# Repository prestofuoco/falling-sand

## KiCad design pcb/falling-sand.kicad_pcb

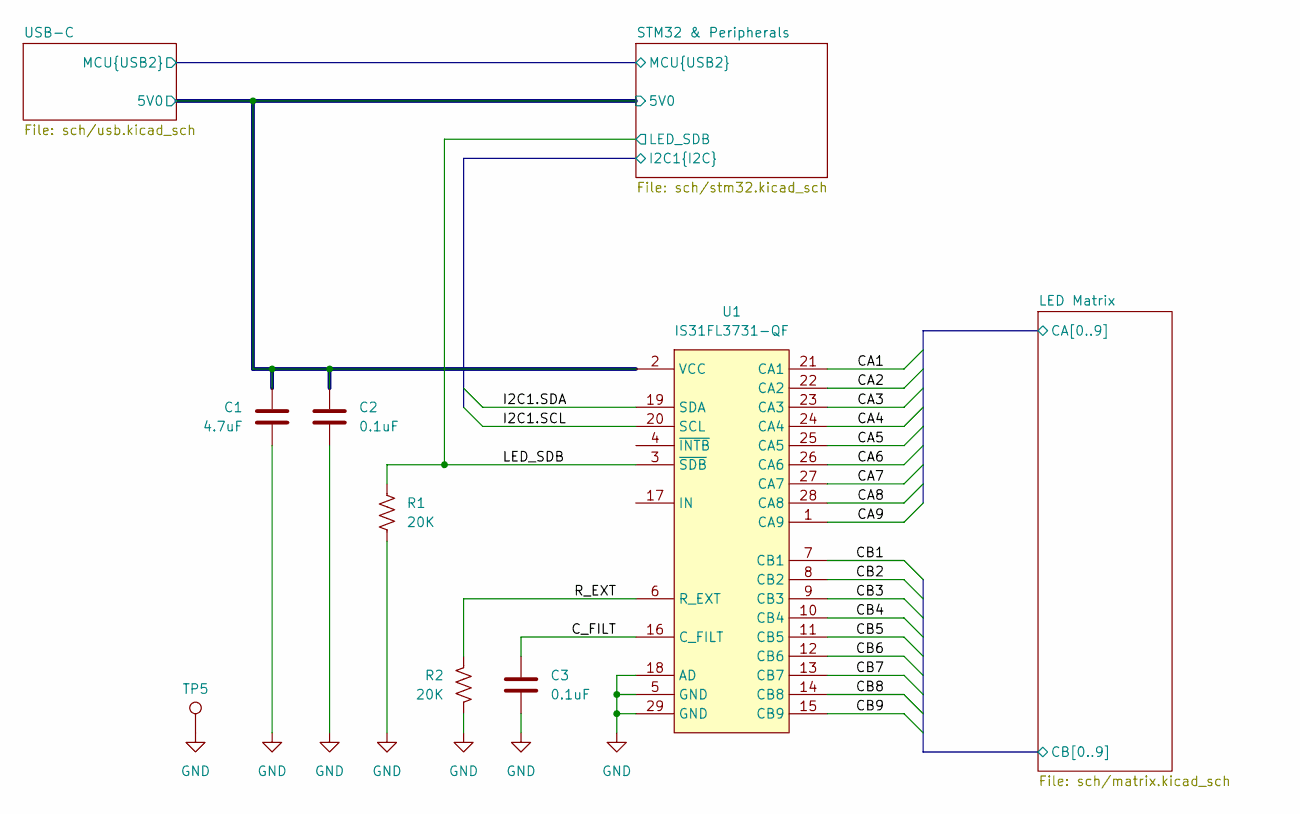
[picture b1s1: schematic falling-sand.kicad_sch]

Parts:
C1: 4.7uF; C_0603_1608Metric
C2, C3: 0.1uF; C_0402_1005Metric
R1, R2: 20K; R_0402_1005Metric
TP5: TestPoint; TestPoint_Pad_D1.0mm
U1: IS31FL3731-QF; QFN-28-1EP_4x4mm_P0.4mm_EP2.4x2.4mm

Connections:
/C_FILT: C3.1, U1.16 (C_FILT)
/LED Matrix/CA1: U1.21 (CA1); also elsewhere on the board
/LED Matrix/CA2: U1.22 (CA2); also elsewhere on the board
/LED Matrix/CA3: U1.23 (CA3); also elsewhere on the board
/LED Matrix/CA4: U1.24 (CA4); also elsewhere on the board
/LED Matrix/CA5: U1.25 (CA5); also elsewhere on the board
/LED Matrix/CA6: U1.26 (CA6); also elsewhere on the board
/LED Matrix/CA7: U1.27 (CA7); also elsewhere on the board
/LED Matrix/CA8: U1.28 (CA8); also elsewhere on the board
/LED Matrix/CA9: U1.1 (CA9); also elsewhere on the board
/LED Matrix/CB1: U1.7 (CB1); also elsewhere on the board
/LED Matrix/CB2: U1.8 (CB2); also elsewhere on the board
/LED Matrix/CB3: U1.9 (CB3); also elsewhere on the board
/LED Matrix/CB4: U1.10 (CB4); also elsewhere on the board
/LED Matrix/CB5: U1.11 (CB5); also elsewhere on the board
/LED Matrix/CB6: U1.12 (CB6); also elsewhere on the board
/LED Matrix/CB7: U1.13 (CB7); also elsewhere on the board
/LED Matrix/CB8: U1.14 (CB8); also elsewhere on the board
/LED Matrix/CB9: U1.15 (CB9); also elsewhere on the board
/LED_SDB: R1.1, U1.3 (~SDB); also elsewhere on the board
/R_EXT: R2.1, U1.6 (R_EXT)
/STM32 & Peripherals/5V0: C1.1, C2.1, U1.2 (VCC); also elsewhere on the board
/STM32 & Peripherals/I2C1.SCL: U1.20 (SCL); also elsewhere on the board
/STM32 & Peripherals/I2C1.SDA: U1.19 (SDA); also elsewhere on the board
GND: C1.2, C2.2, C3.2, R1.2, R2.2, TP5.1 (1_1), U1.5 (GND), U1.18 (AD), U1.29 (GND); also elsewhere on the board

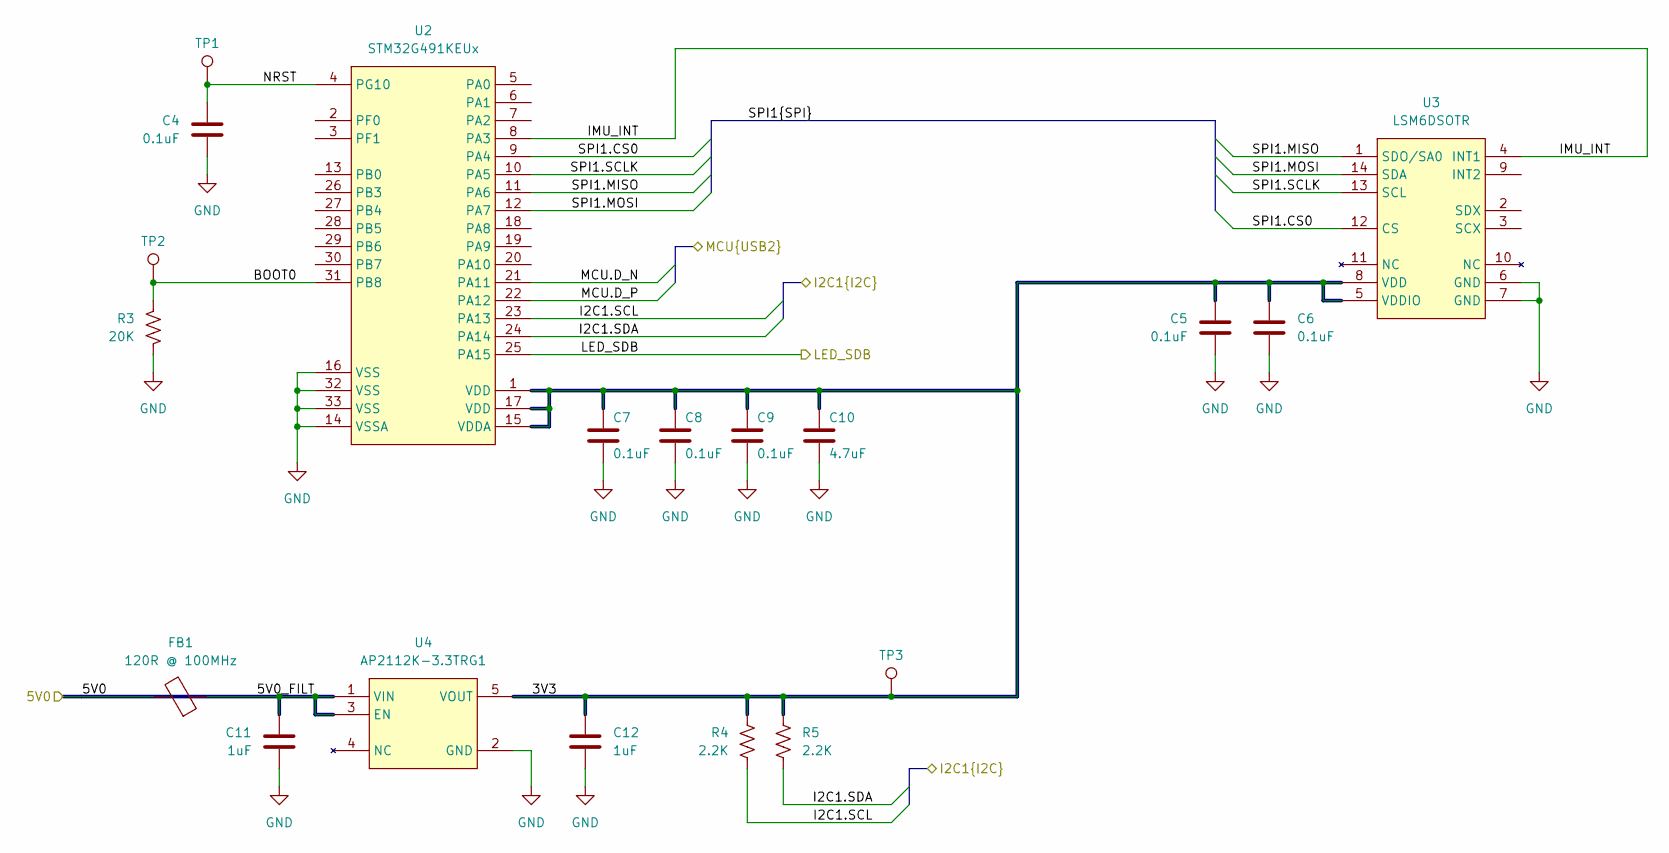
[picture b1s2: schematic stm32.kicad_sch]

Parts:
C4, C5, C6, C7, C8, C9: 0.1uF; C_0402_1005Metric
C10: 4.7uF; C_0603_1608Metric
C11, C12: 1uF; C_0603_1608Metric
FB1: 120R @ 100MHz; L_0805_2012Metric
R3: 20K; R_0402_1005Metric
R4, R5: 2.2K; R_0402_1005Metric
TP1, TP2, TP3: TestPoint; TestPoint_Pad_D1.0mm
U2: STM32G491KEUx; QFN-32-1EP_5x5mm_P0.5mm_EP3.45x3.45mm
U3: LSM6DSOTR; LGA-14_3x2.5mm_P0.5mm_LayoutBorder3x4y
U4: AP2112K-3.3TRG1; SOT-23-5

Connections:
/LED_SDB: U2.25 (PA15); also elsewhere on the board
/STM32 & Peripherals/3V3: C5.1, C6.1, C7.1, C8.1, C9.1, C10.1, C12.1, R4.1, R5.1, TP3.1 (1_1), U2.1 (VDD), U2.15 (VDDA), U2.17 (VDD), U3.5 (VDDIO), U3.8 (VDD), U4.5 (VOUT)
/STM32 & Peripherals/5V0: FB1.2; also elsewhere on the board
/STM32 & Peripherals/5V0_FILT: C11.1, FB1.1, U4.1 (VIN), U4.3 (EN)
/STM32 & Peripherals/BOOT0: R3.1, TP2.1 (1_1), U2.31 (PB8)
/STM32 & Peripherals/I2C1.SCL: R4.2, U2.23 (PA13); also elsewhere on the board
/STM32 & Peripherals/I2C1.SDA: R5.2, U2.24 (PA14); also elsewhere on the board
/STM32 & Peripherals/IMU_INT: U2.8 (PA3), U3.4 (INT1)
/STM32 & Peripherals/MCU.D_N: U2.21 (PA11); also elsewhere on the board
/STM32 & Peripherals/MCU.D_P: U2.22 (PA12); also elsewhere on the board
/STM32 & Peripherals/NRST: C4.1, TP1.1 (1_1), U2.4 (PG10)
/STM32 & Peripherals/SPI1.CS0: U2.9 (PA4), U3.12 (CS)
/STM32 & Peripherals/SPI1.MISO: U2.11 (PA6), U3.1 (SDO/SA0)
/STM32 & Peripherals/SPI1.MOSI: U2.12 (PA7), U3.14 (SDA)
/STM32 & Peripherals/SPI1.SCLK: U2.10 (PA5), U3.13 (SCL)
GND: C4.2, C5.2, C6.2, C7.2, C8.2, C9.2, C10.2, C11.2, C12.2, R3.2, U2.14 (VSSA), U2.16 (VSS), U2.32 (VSS), U2.33 (VSS), U3.6 (GND), U3.7 (GND), U4.2 (GND); also elsewhere on the board

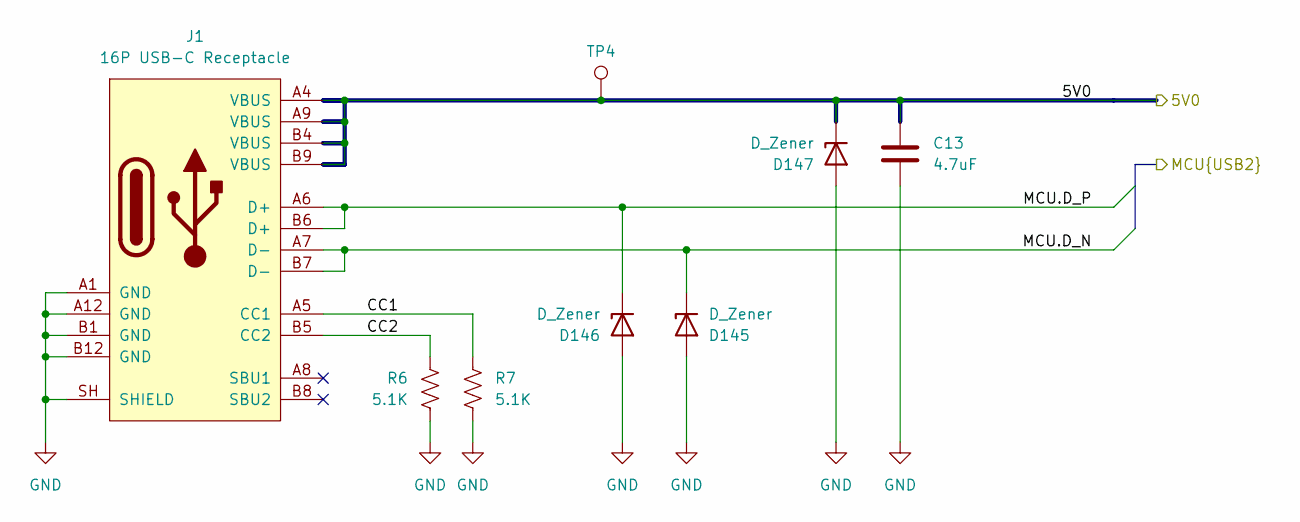
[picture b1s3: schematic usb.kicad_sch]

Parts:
C13: 4.7uF; C_0603_1608Metric
D145, D146, D147: D_Zener; D_SOD-882
J1: 16P USB-C Receptacle; USB_C_Receptacle_GCT_USB4105-xx-A_16P_TopMnt_Horizontal
R6, R7: 5.1K; R_0402_1005Metric
TP4: TestPoint; TestPoint_Pad_D1.0mm

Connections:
/STM32 & Peripherals/5V0: C13.1, D147.1 (K), J1.A4 (VBUS), J1.A9 (VBUS), J1.B4 (VBUS), J1.B9 (VBUS), TP4.1 (1_1); also elsewhere on the board
/STM32 & Peripherals/MCU.D_N: D145.1 (K), J1.A7 (D-), J1.B7 (D-); also elsewhere on the board
/STM32 & Peripherals/MCU.D_P: D146.1 (K), J1.A6 (D+), J1.B6 (D+); also elsewhere on the board
/USB-C/CC1: J1.A5 (CC1), R7.1
/USB-C/CC2: J1.B5 (CC2), R6.1
GND: C13.2, D145.2 (A), D146.2 (A), D147.2 (A), J1.A1 (GND), J1.A12 (GND), J1.B1 (GND), J1.B12 (GND), J1.SH (SHIELD), R6.2, R7.2; also elsewhere on the board

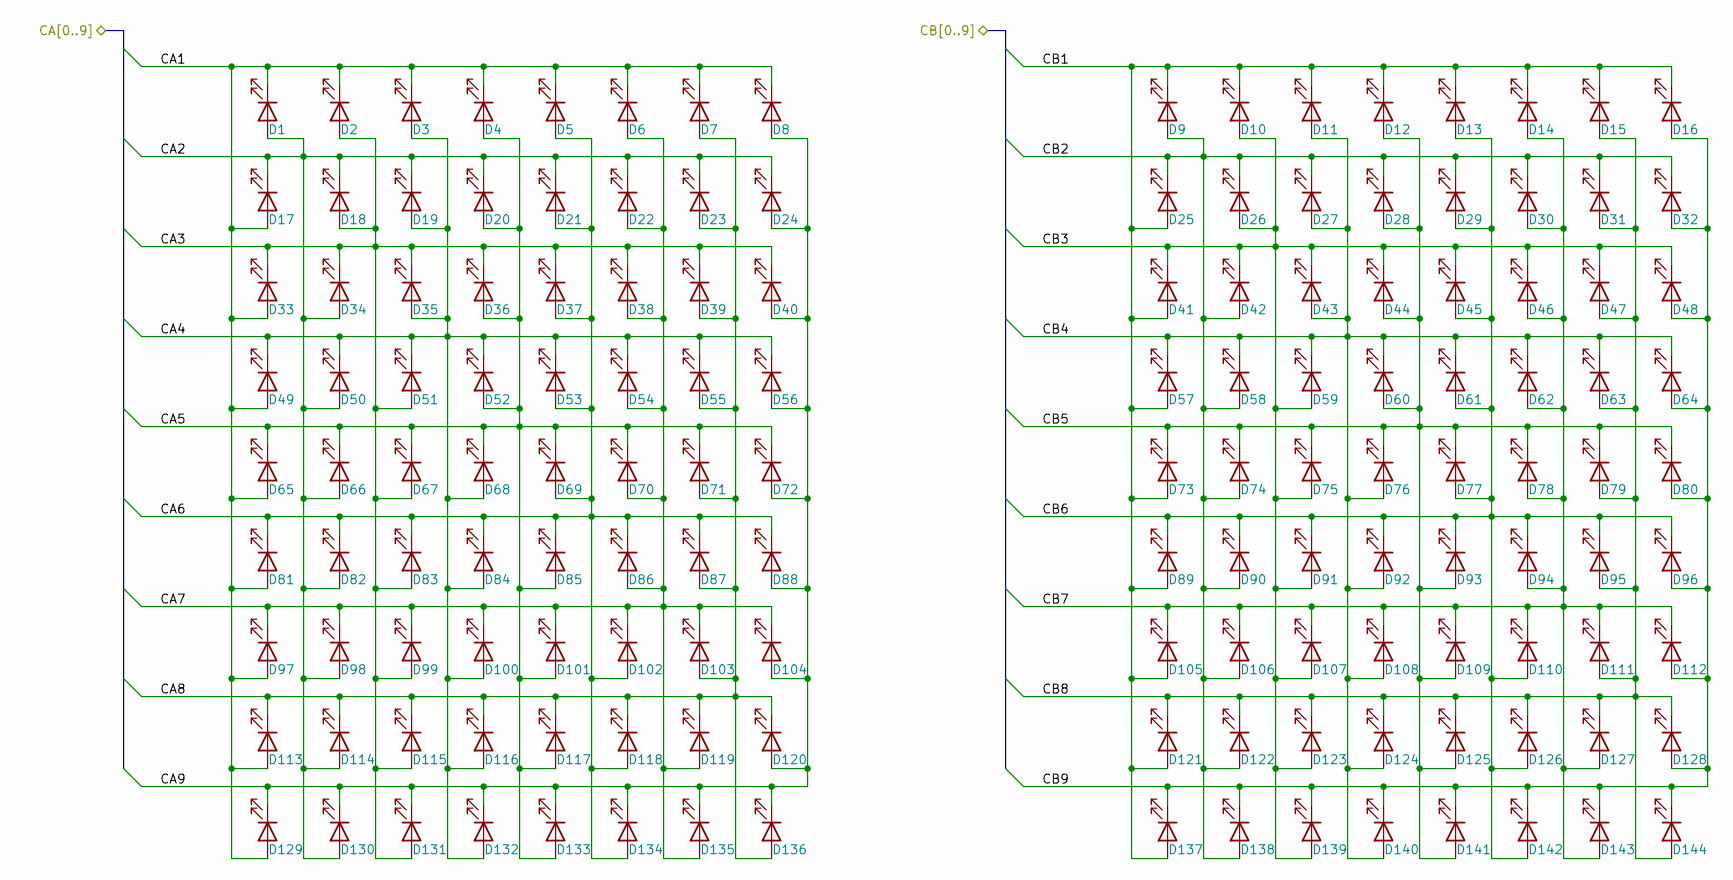
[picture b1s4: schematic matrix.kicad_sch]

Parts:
D1, D2, D3, D4, D5, D6, D7, D8, D9, D10, D11, D12, D13, D14, D15, D16, D17, D18, D19, D20, D21, D22, D23, D24, D25, D26, D27, D28, D29, D30, D31, D32, D33, D34, D35, D36, D37, D38, D39, D40, D41, D42, D43, D44, D45, D46, D47, D48, D49, D50, D51, D52, D53, D54, D55, D56, D57, D58, D59, D60, D61, D62, D63, D64, D65, D66, D67, D68, D69, D70, D71, D72, D73, D74, D75, D76, D77, D78, D79, D80, D81, D82, D83, D84, D85, D86, D87, D88, D89, D90, D91, D92, D93, D94, D95, D96, D97, D98, D99, D100, D101, D102, D103, D104, D105, D106, D107, D108, D109, D110, D111, D112, D113, D114, D115, D116, D117, D118, D119, D120, D121, D122, D123, D124, D125, D126, D127, D128, D129, D130, D131, D132, D133, D134, D135, D136, D137, D138, D139, D140, D141, D142, D143, D144: LED; LED_0402_1005Metric

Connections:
/LED Matrix/CA1: D1.1 (K), D2.1 (K), D3.1 (K), D4.1 (K), D5.1 (K), D6.1 (K), D7.1 (K), D8.1 (K), D17.2 (A), D33.2 (A), D49.2 (A), D65.2 (A), D81.2 (A), D97.2 (A), D113.2 (A), D129.2 (A); also elsewhere on the board
/LED Matrix/CA2: D1.2 (A), D17.1 (K), D18.1 (K), D19.1 (K), D20.1 (K), D21.1 (K), D22.1 (K), D23.1 (K), D24.1 (K), D34.2 (A), D50.2 (A), D66.2 (A), D82.2 (A), D98.2 (A), D114.2 (A), D130.2 (A); also elsewhere on the board
/LED Matrix/CA3: D2.2 (A), D18.2 (A), D33.1 (K), D34.1 (K), D35.1 (K), D36.1 (K), D37.1 (K), D38.1 (K), D39.1 (K), D40.1 (K), D51.2 (A), D67.2 (A), D83.2 (A), D99.2 (A), D115.2 (A), D131.2 (A); also elsewhere on the board
/LED Matrix/CA4: D3.2 (A), D19.2 (A), D35.2 (A), D49.1 (K), D50.1 (K), D51.1 (K), D52.1 (K), D53.1 (K), D54.1 (K), D55.1 (K), D56.1 (K), D68.2 (A), D84.2 (A), D100.2 (A), D116.2 (A), D132.2 (A); also elsewhere on the board
/LED Matrix/CA5: D4.2 (A), D20.2 (A), D36.2 (A), D52.2 (A), D65.1 (K), D66.1 (K), D67.1 (K), D68.1 (K), D69.1 (K), D70.1 (K), D71.1 (K), D72.1 (K), D85.2 (A), D101.2 (A), D117.2 (A), D133.2 (A); also elsewhere on the board
/LED Matrix/CA6: D5.2 (A), D21.2 (A), D37.2 (A), D53.2 (A), D69.2 (A), D81.1 (K), D82.1 (K), D83.1 (K), D84.1 (K), D85.1 (K), D86.1 (K), D87.1 (K), D88.1 (K), D102.2 (A), D118.2 (A), D134.2 (A); also elsewhere on the board
/LED Matrix/CA7: D6.2 (A), D22.2 (A), D38.2 (A), D54.2 (A), D70.2 (A), D86.2 (A), D97.1 (K), D98.1 (K), D99.1 (K), D100.1 (K), D101.1 (K), D102.1 (K), D103.1 (K), D104.1 (K), D119.2 (A), D135.2 (A); also elsewhere on the board
/LED Matrix/CA8: D7.2 (A), D23.2 (A), D39.2 (A), D55.2 (A), D71.2 (A), D87.2 (A), D103.2 (A), D113.1 (K), D114.1 (K), D115.1 (K), D116.1 (K), D117.1 (K), D118.1 (K), D119.1 (K), D120.1 (K), D136.2 (A); also elsewhere on the board
/LED Matrix/CA9: D8.2 (A), D24.2 (A), D40.2 (A), D56.2 (A), D72.2 (A), D88.2 (A), D104.2 (A), D120.2 (A), D129.1 (K), D130.1 (K), D131.1 (K), D132.1 (K), D133.1 (K), D134.1 (K), D135.1 (K), D136.1 (K); also elsewhere on the board
/LED Matrix/CB1: D9.1 (K), D10.1 (K), D11.1 (K), D12.1 (K), D13.1 (K), D14.1 (K), D15.1 (K), D16.1 (K), D25.2 (A), D41.2 (A), D57.2 (A), D73.2 (A), D89.2 (A), D105.2 (A), D121.2 (A), D137.2 (A); also elsewhere on the board
/LED Matrix/CB2: D9.2 (A), D25.1 (K), D26.1 (K), D27.1 (K), D28.1 (K), D29.1 (K), D30.1 (K), D31.1 (K), D32.1 (K), D42.2 (A), D58.2 (A), D74.2 (A), D90.2 (A), D106.2 (A), D122.2 (A), D138.2 (A); also elsewhere on the board
/LED Matrix/CB3: D10.2 (A), D26.2 (A), D41.1 (K), D42.1 (K), D43.1 (K), D44.1 (K), D45.1 (K), D46.1 (K), D47.1 (K), D48.1 (K), D59.2 (A), D75.2 (A), D91.2 (A), D107.2 (A), D123.2 (A), D139.2 (A); also elsewhere on the board
/LED Matrix/CB4: D11.2 (A), D27.2 (A), D43.2 (A), D57.1 (K), D58.1 (K), D59.1 (K), D60.1 (K), D61.1 (K), D62.1 (K), D63.1 (K), D64.1 (K), D76.2 (A), D92.2 (A), D108.2 (A), D124.2 (A), D140.2 (A); also elsewhere on the board
/LED Matrix/CB5: D12.2 (A), D28.2 (A), D44.2 (A), D60.2 (A), D73.1 (K), D74.1 (K), D75.1 (K), D76.1 (K), D77.1 (K), D78.1 (K), D79.1 (K), D80.1 (K), D93.2 (A), D109.2 (A), D125.2 (A), D141.2 (A); also elsewhere on the board
/LED Matrix/CB6: D13.2 (A), D29.2 (A), D45.2 (A), D61.2 (A), D77.2 (A), D89.1 (K), D90.1 (K), D91.1 (K), D92.1 (K), D93.1 (K), D94.1 (K), D95.1 (K), D96.1 (K), D110.2 (A), D126.2 (A), D142.2 (A); also elsewhere on the board
/LED Matrix/CB7: D14.2 (A), D30.2 (A), D46.2 (A), D62.2 (A), D78.2 (A), D94.2 (A), D105.1 (K), D106.1 (K), D107.1 (K), D108.1 (K), D109.1 (K), D110.1 (K), D111.1 (K), D112.1 (K), D127.2 (A), D143.2 (A); also elsewhere on the board
/LED Matrix/CB8: D15.2 (A), D31.2 (A), D47.2 (A), D63.2 (A), D79.2 (A), D95.2 (A), D111.2 (A), D121.1 (K), D122.1 (K), D123.1 (K), D124.1 (K), D125.1 (K), D126.1 (K), D127.1 (K), D128.1 (K), D144.2 (A); also elsewhere on the board
/LED Matrix/CB9: D16.2 (A), D32.2 (A), D48.2 (A), D64.2 (A), D80.2 (A), D96.2 (A), D112.2 (A), D128.2 (A), D137.1 (K), D138.1 (K), D139.1 (K), D140.1 (K), D141.1 (K), D142.1 (K), D143.1 (K), D144.1 (K); also elsewhere on the board

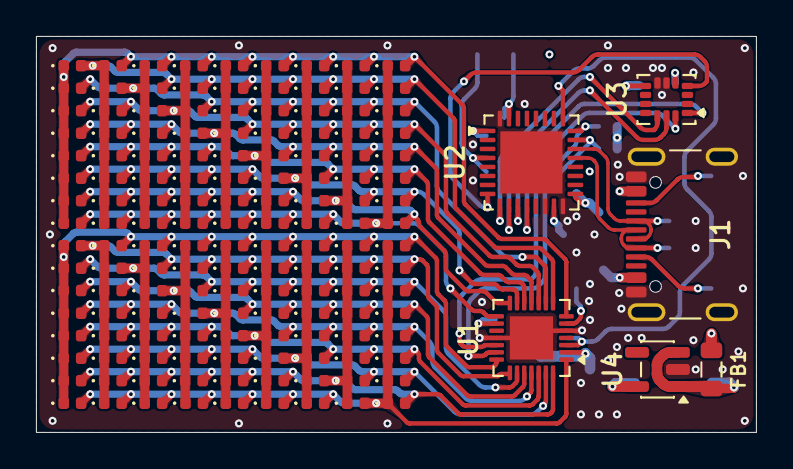
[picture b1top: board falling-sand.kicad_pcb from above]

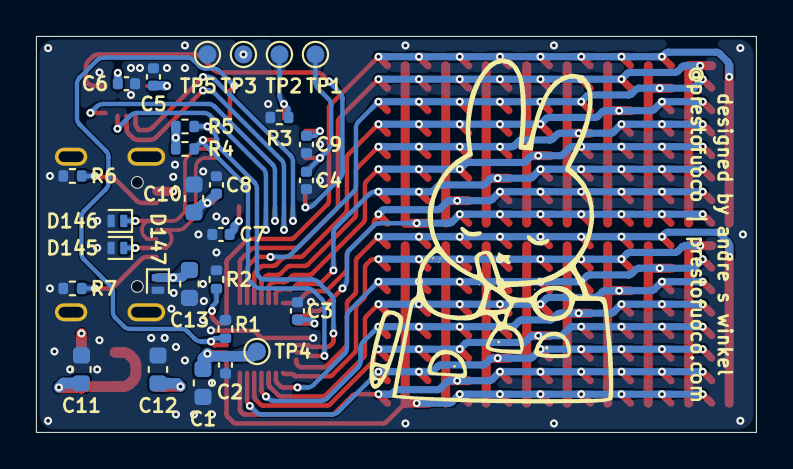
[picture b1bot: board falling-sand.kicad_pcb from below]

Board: 4 copper layers, 40.0 x 22.0 mm, 178 parts (28 on the bottom side), 38 nets.

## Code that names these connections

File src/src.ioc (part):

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Mcu.Name=STM32G491K(C-E)Ux
Mcu.Package=UFQFPN32
Mcu.UserName=STM32G491KEUx
PA11.Mode=Device
PA11.Signal=USB_DM
PA12.Mode=Device
PA12.Signal=USB_DP
PA13.Mode=I2C
PA13.Signal=I2C1_SCL
PA14.Mode=I2C
PA14.Signal=I2C1_SDA
PA15.GPIOParameters=GPIO_Label
PA15.GPIO_Label=LED_SDB
PA15.Signal=GPIO_Output
PA3.GPIOParameters=GPIO_Label
PA3.GPIO_Label=IMU_INT
PA3.Signal=GPIO_Input
PA4.GPIOParameters=GPIO_Label
PA4.GPIO_Label=IMU_CS
PA4.Signal=GPIO_Output
PA5.Mode=Full_Duplex_Master
PA5.Signal=SPI1_SCK
PA6.Mode=Full_Duplex_Master
PA6.Signal=SPI1_MISO
PA7.Mode=Full_Duplex_Master
PA7.Signal=SPI1_MOSI
RCC.HSE_VALUE=8000000
RCC.SYSCLKFreq_VALUE=16000000
board=custom

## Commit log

2026-03-06 cleaned
2026-03-10 firmware init commit
2026-03-10 restructured src
2026-03-10 added uc flash script
2026-03-10 8 bit spi, lm6dso drivers
2026-03-10 init driver structure
2026-03-11 led matrix driver defined is31_init and set frame
2026-03-15 structure def
